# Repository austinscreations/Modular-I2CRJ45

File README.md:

# Modular-I2CRJ45
an oxrs compatible I2CRJ45 board in a modular format

2023-10-25 version 220 was created to fix p fet issue
also updated JLCPCB PCBa files for the modular I2CRJ45 and port PWR extention

this baord is 2 layers

port PWR is 2 layers

port PWR extention is a remote switch that allows you to turn ports on and off. the use of a 1.25mm jst cable could eb used instead, simply with pin 5 being GND connect the others to this and a port will be ON

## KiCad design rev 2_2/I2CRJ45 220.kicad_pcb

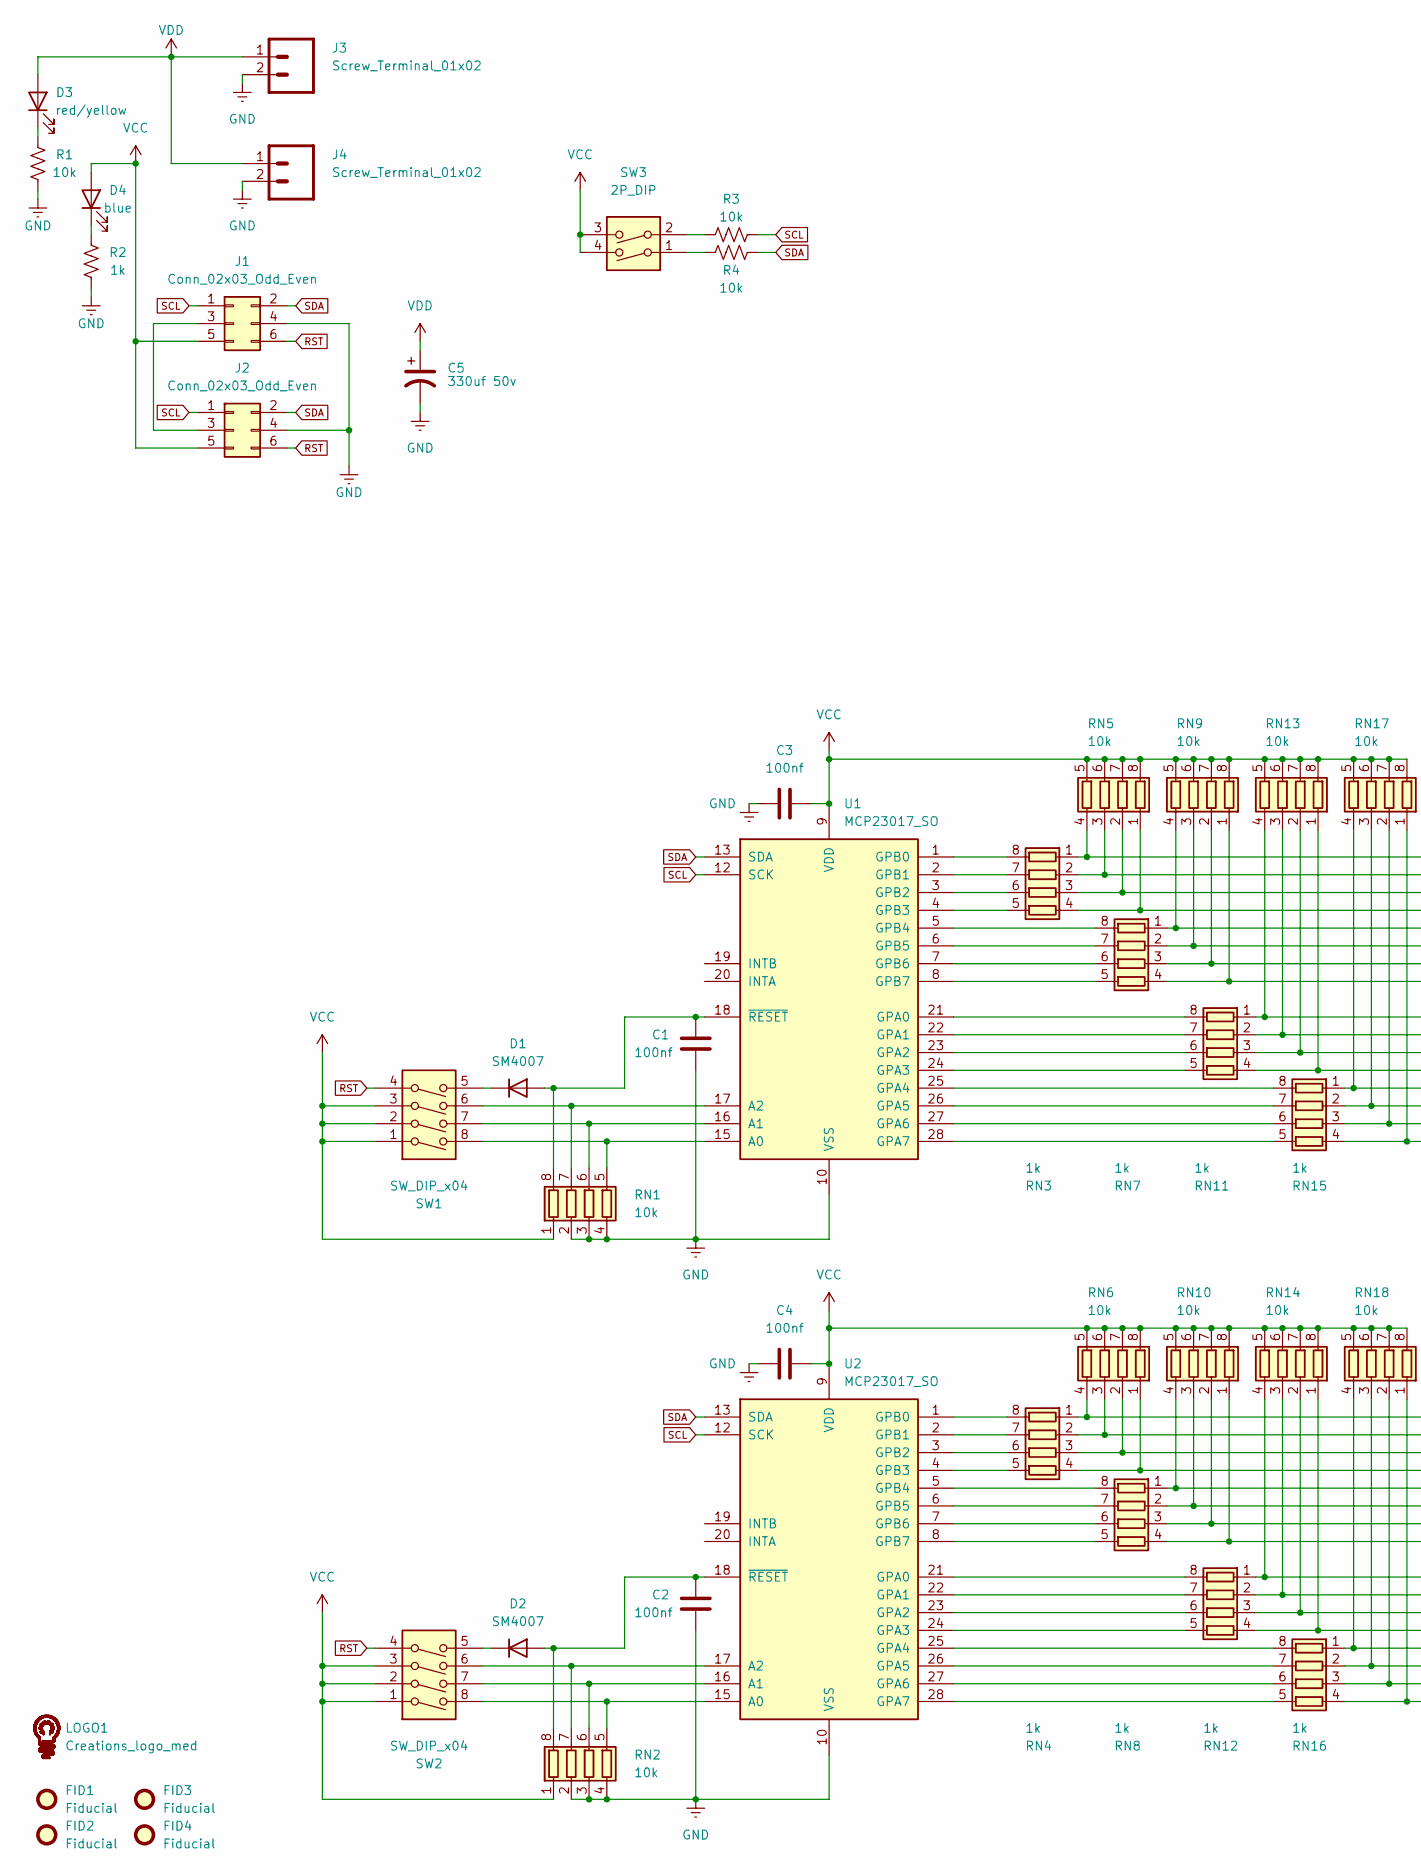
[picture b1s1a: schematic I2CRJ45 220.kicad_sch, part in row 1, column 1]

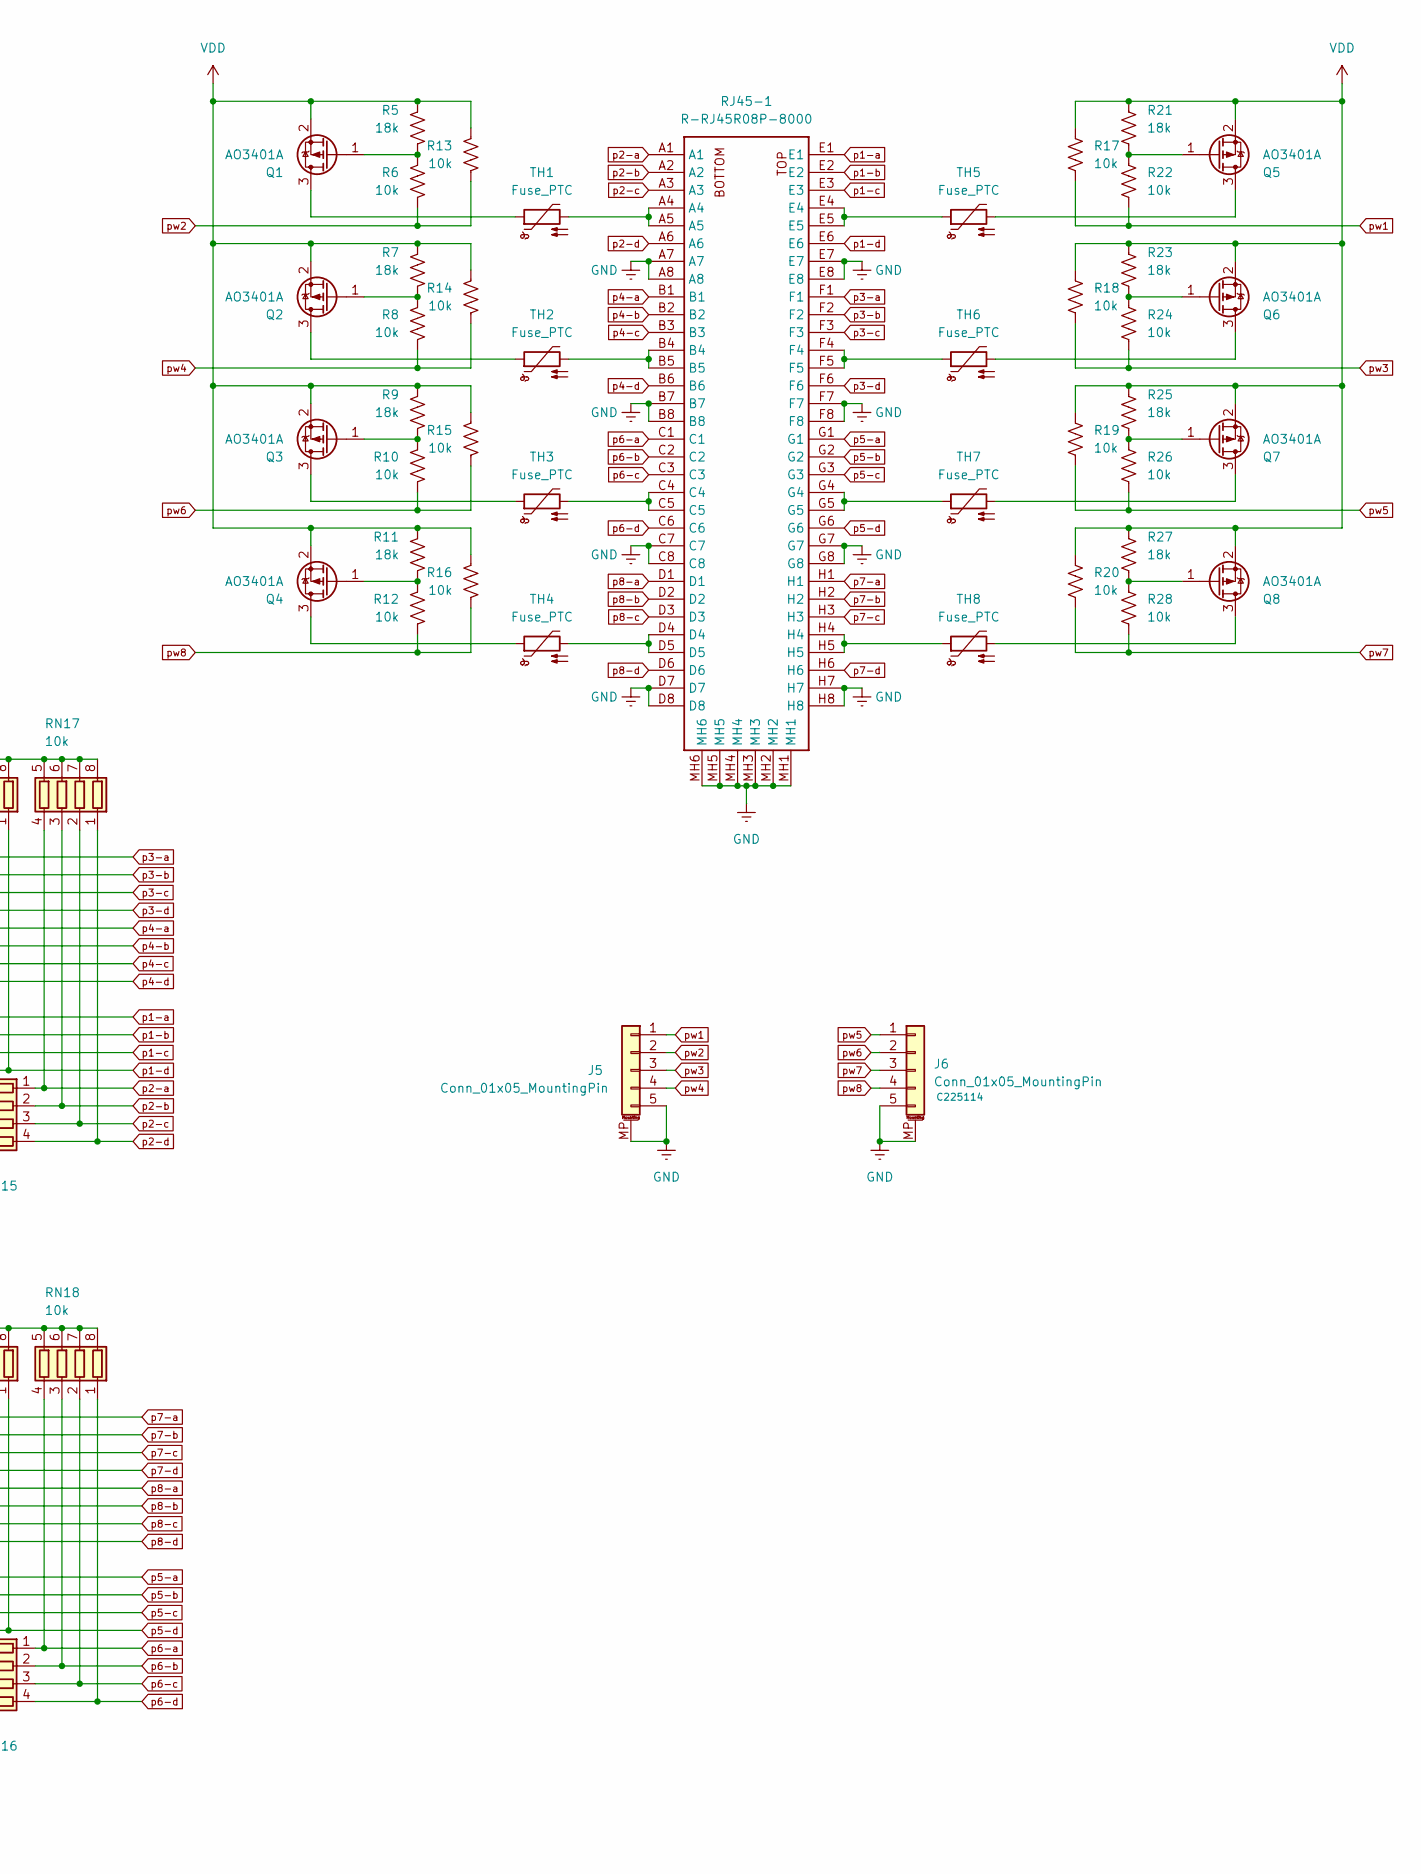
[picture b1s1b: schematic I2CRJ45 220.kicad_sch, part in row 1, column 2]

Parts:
C1, C2, C3, C4: 100nf; C_0603_1608Metric; LCSC C14663
C5: 330uf 50v; CP_Elec_10x10; LCSC C2895745
D1, D2: SM4007; D_SOD-123F; LCSC C64898
D3: red/yellow; LED_0603_1608Metric; LCSC C72038
D4: blue; LED_0603_1608Metric; LCSC C72041
FID1, FID2, FID3, FID4: Fiducial; Fiducial_1mm_Mask2mm
J1, J2: Conn_02x03_Odd_Even; IDC-Header_2x03_P2.54mm_Vertical; LCSC C132438
J3, J4: Screw_Terminal_01x02; 2pinblock; LCSC C3703
J5, J6: Conn_01x05_MountingPin; JST_GH_SM05B-GHS-TB_1x05-1MP_P1.25mm_Horizontal; LCSC C225114
LOGO1: Creations_logo_med; Creations logo med
Q1, Q2, Q3, Q4, Q5, Q6, Q7, Q8: AO3401A; SOT-23; LCSC C15127
R1, R3, R4, R6, R8, R10, R12, R13, R14, R15, R16, R17, R18, R19, R20, R22, R24, R26, R28: 10k; R_0603_1608Metric; LCSC C25804
R2: 1k; R_0603_1608Metric; LCSC C21190
R5, R7, R9, R11, R21, R23, R25, R27: 18k; R_0603_1608Metric; LCSC C25810
RJ45-1: R-RJ45R08P-8000; LCSC C386760
RN1, RN2, RN5, RN6, RN9, RN10, RN13, RN14, RN17, RN18: 10k; R_Array_Convex_4x0603; LCSC C29718
RN3, RN4, RN7, RN8, RN11, RN12, RN15, RN16: 1k; R_Array_Convex_4x0603; LCSC C20197
SW1, SW2: SW_DIP_x04; 4P_DIP; LCSC C2758183
SW3: 2P_DIP; LCSC C2758181
TH1, TH2, TH3, TH4, TH5, TH6, TH7, TH8: Fuse_PTC; R_0603_1608Metric; LCSC C883087
U1, U2: MCP23017_SO; SOIC-28W_7.5x17.9mm_P1.27mm; LCSC C47023

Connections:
GNDREF: C1.2, C2.2, C3.1, C4.1, C5.2, J1.4, J2.4, J3.2, J4.2, J5.5, J5.MP (MountPin), J6.5, J6.MP (MountPin), R1.2, R2.2, RJ45-1.A7, RJ45-1.A8, RJ45-1.B7, RJ45-1.B8, RJ45-1.C7, RJ45-1.C8, RJ45-1.D7, RJ45-1.D8, RJ45-1.E7, RJ45-1.E8, RJ45-1.F7, RJ45-1.F8, RJ45-1.G7, RJ45-1.G8, RJ45-1.H7, RJ45-1.H8, RJ45-1.MH1, RJ45-1.MH2, RJ45-1.MH3, RJ45-1.MH4, RJ45-1.MH5, RJ45-1.MH6, RN1.2 (R2.1), RN1.3 (R3.1), RN1.4 (R4.1), RN2.2 (R2.1), RN2.3 (R3.1), RN2.4 (R4.1), U1.10 (VSS), U2.10 (VSS)
unnamed: C1.1, D1.2 (A), RN1.8 (R1.2), U1.18 (~RESET)
unnamed: C2.1, D2.2 (A), RN2.8 (R1.2), U2.18 (~RESET)
unnamed: D1.1 (K), SW1.5
unnamed: D2.1 (K), SW2.5
unnamed: D3.1 (K), R1.1
unnamed: D4.1 (K), R2.1
unnamed: J1.3, J2.3
unnamed: Q1.1 (G), R5.2, R6.1
unnamed: Q2.1 (G), R7.2, R8.1
unnamed: Q3.1 (G), R9.2, R10.1
unnamed: Q4.1 (G), R11.2, R12.1
unnamed: Q5.1 (G), R21.2, R22.1
unnamed: Q6.1 (G), R23.2, R24.1
unnamed: Q7.1 (G), R25.2, R26.1
unnamed: Q8.1 (G), R27.2, R28.1
unnamed: R3.1, SW3.2
unnamed: R4.1, SW3.1
unnamed: RJ45-1.A4, RJ45-1.A5, TH1.2
unnamed: RJ45-1.B4, RJ45-1.B5, TH2.2
unnamed: RJ45-1.C4, RJ45-1.C5, TH3.2
unnamed: RJ45-1.D4, RJ45-1.D5, TH4.2
unnamed: RJ45-1.E4, RJ45-1.E5, TH5.1
unnamed: RJ45-1.F4, RJ45-1.F5, TH6.1
unnamed: RJ45-1.G4, RJ45-1.G5, TH7.1
unnamed: RJ45-1.H4, RJ45-1.H5, TH8.1
unnamed: RN1.5 (R4.2), SW1.8, U1.15 (A0)
unnamed: RN1.6 (R3.2), SW1.7, U1.16 (A1)
unnamed: RN1.7 (R2.2), SW1.6, U1.17 (A2)
unnamed: RN2.5 (R4.2), SW2.8, U2.15 (A0)
unnamed: RN2.6 (R3.2), SW2.7, U2.16 (A1)
unnamed: RN2.7 (R2.2), SW2.6, U2.17 (A2)
unnamed: RN3.5 (R4.2), U1.4 (GPB3)
unnamed: RN3.6 (R3.2), U1.3 (GPB2)
unnamed: RN3.7 (R2.2), U1.2 (GPB1)
unnamed: RN3.8 (R1.2), U1.1 (GPB0)
unnamed: RN4.5 (R4.2), U2.4 (GPB3)
unnamed: RN4.6 (R3.2), U2.3 (GPB2)
unnamed: RN4.7 (R2.2), U2.2 (GPB1)
unnamed: RN4.8 (R1.2), U2.1 (GPB0)
unnamed: RN7.5 (R4.2), U1.8 (GPB7)
unnamed: RN7.6 (R3.2), U1.7 (GPB6)
unnamed: RN7.7 (R2.2), U1.6 (GPB5)
unnamed: RN7.8 (R1.2), U1.5 (GPB4)
unnamed: RN8.5 (R4.2), U2.8 (GPB7)
unnamed: RN8.6 (R3.2), U2.7 (GPB6)
unnamed: RN8.7 (R2.2), U2.6 (GPB5)
unnamed: RN8.8 (R1.2), U2.5 (GPB4)
unnamed: RN11.5 (R4.2), U1.24 (GPA3)
unnamed: RN11.6 (R3.2), U1.23 (GPA2)
unnamed: RN11.7 (R2.2), U1.22 (GPA1)
unnamed: RN11.8 (R1.2), U1.21 (GPA0)
unnamed: RN12.5 (R4.2), U2.24 (GPA3)
unnamed: RN12.6 (R3.2), U2.23 (GPA2)
unnamed: RN12.7 (R2.2), U2.22 (GPA1)
unnamed: RN12.8 (R1.2), U2.21 (GPA0)
unnamed: RN15.5 (R4.2), U1.28 (GPA7)
unnamed: RN15.6 (R3.2), U1.27 (GPA6)
unnamed: RN15.7 (R2.2), U1.26 (GPA5)
unnamed: RN15.8 (R1.2), U1.25 (GPA4)
unnamed: RN16.5 (R4.2), U2.28 (GPA7)
unnamed: RN16.6 (R3.2), U2.27 (GPA6)
unnamed: RN16.7 (R2.2), U2.26 (GPA5)
unnamed: RN16.8 (R1.2), U2.25 (GPA4)
unnamed: Q1.3 (D), TH1.1
unnamed: Q2.3 (D), TH2.1
unnamed: Q3.3 (D), TH3.1
unnamed: Q4.3 (D), TH4.1
unnamed: Q5.3 (D), TH5.2
unnamed: Q6.3 (D), TH6.2
unnamed: Q7.3 (D), TH7.2
unnamed: Q8.3 (D), TH8.2
RST: J1.6, J2.6, SW1.4, SW2.4
SCL: J1.1, J2.1, R3.2, U1.12 (SCK), U2.12 (SCK)
SDA: J1.2, J2.2, R4.2, U1.13 (SDA), U2.13 (SDA)
VCC: C3.2, C4.2, D4.2 (A), J1.5, J2.5, RN1.1 (R1.1), RN2.1 (R1.1), RN5.5 (R4.2), RN5.6 (R3.2), RN5.7 (R2.2), RN5.8 (R1.2), RN6.5 (R4.2), RN6.6 (R3.2), RN6.7 (R2.2), RN6.8 (R1.2), RN9.5 (R4.2), RN9.6 (R3.2), RN9.7 (R2.2), RN9.8 (R1.2), RN10.5 (R4.2), RN10.6 (R3.2), RN10.7 (R2.2), RN10.8 (R1.2), RN13.5 (R4.2), RN13.6 (R3.2), RN13.7 (R2.2), RN13.8 (R1.2), RN14.5 (R4.2), RN14.6 (R3.2), RN14.7 (R2.2), RN14.8 (R1.2), RN17.5 (R4.2), RN17.6 (R3.2), RN17.7 (R2.2), RN17.8 (R1.2), RN18.5 (R4.2), RN18.6 (R3.2), RN18.7 (R2.2), RN18.8 (R1.2), SW1.1, SW1.2, SW1.3, SW2.1, SW2.2, SW2.3, SW3.3, SW3.4, U1.9 (VDD), U2.9 (VDD)
VDD: C5.1, D3.2 (A), J3.1, J4.1, Q1.2 (S), Q2.2 (S), Q3.2 (S), Q4.2 (S), Q5.2 (S), Q6.2 (S), Q7.2 (S), Q8.2 (S), R5.1, R7.1, R9.1, R11.1, R13.1, R14.1, R15.1, R16.1, R17.1, R18.1, R19.1, R20.1, R21.1, R23.1, R25.1, R27.1
p1-a: RJ45-1.E1, RN11.1 (R1.1), RN13.4 (R4.1)
p1-b: RJ45-1.E2, RN11.2 (R2.1), RN13.3 (R3.1)
p1-c: RJ45-1.E3, RN11.3 (R3.1), RN13.2 (R2.1)
p1-d: RJ45-1.E6, RN11.4 (R4.1), RN13.1 (R1.1)
p2-a: RJ45-1.A1, RN15.1 (R1.1), RN17.4 (R4.1)
p2-b: RJ45-1.A2, RN15.2 (R2.1), RN17.3 (R3.1)
p2-c: RJ45-1.A3, RN15.3 (R3.1), RN17.2 (R2.1)
p2-d: RJ45-1.A6, RN15.4 (R4.1), RN17.1 (R1.1)
p3-a: RJ45-1.F1, RN3.1 (R1.1), RN5.4 (R4.1)
p3-b: RJ45-1.F2, RN3.2 (R2.1), RN5.3 (R3.1)
p3-c: RJ45-1.F3, RN3.3 (R3.1), RN5.2 (R2.1)
p3-d: RJ45-1.F6, RN3.4 (R4.1), RN5.1 (R1.1)
p4-a: RJ45-1.B1, RN7.1 (R1.1), RN9.4 (R4.1)
p4-b: RJ45-1.B2, RN7.2 (R2.1), RN9.3 (R3.1)
p4-c: RJ45-1.B3, RN7.3 (R3.1), RN9.2 (R2.1)
p4-d: RJ45-1.B6, RN7.4 (R4.1), RN9.1 (R1.1)
p5-a: RJ45-1.G1, RN12.1 (R1.1), RN14.4 (R4.1)
p5-b: RJ45-1.G2, RN12.2 (R2.1), RN14.3 (R3.1)
p5-c: RJ45-1.G3, RN12.3 (R3.1), RN14.2 (R2.1)
p5-d: RJ45-1.G6, RN12.4 (R4.1), RN14.1 (R1.1)
p6-a: RJ45-1.C1, RN16.1 (R1.1), RN18.4 (R4.1)
p6-b: RJ45-1.C2, RN16.2 (R2.1), RN18.3 (R3.1)
p6-c: RJ45-1.C3, RN16.3 (R3.1), RN18.2 (R2.1)
p6-d: RJ45-1.C6, RN16.4 (R4.1), RN18.1 (R1.1)
p7-a: RJ45-1.H1, RN4.1 (R1.1), RN6.4 (R4.1)
p7-b: RJ45-1.H2, RN4.2 (R2.1), RN6.3 (R3.1)
p7-c: RJ45-1.H3, RN4.3 (R3.1), RN6.2 (R2.1)
p7-d: RJ45-1.H6, RN4.4 (R4.1), RN6.1 (R1.1)
p8-a: RJ45-1.D1, RN8.1 (R1.1), RN10.4 (R4.1)
p8-b: RJ45-1.D2, RN8.2 (R2.1), RN10.3 (R3.1)
p8-c: RJ45-1.D3, RN8.3 (R3.1), RN10.2 (R2.1)
p8-d: RJ45-1.D6, RN8.4 (R4.1), RN10.1 (R1.1)
pw1: J5.1, R17.2, R22.2
pw2: J5.2, R6.2, R13.2
pw3: J5.3, R18.2, R24.2
pw4: J5.4, R8.2, R14.2
pw5: J6.1, R19.2, R26.2
pw6: J6.2, R10.2, R15.2
pw7: J6.3, R20.2, R28.2
pw8: J6.4, R12.2, R16.2

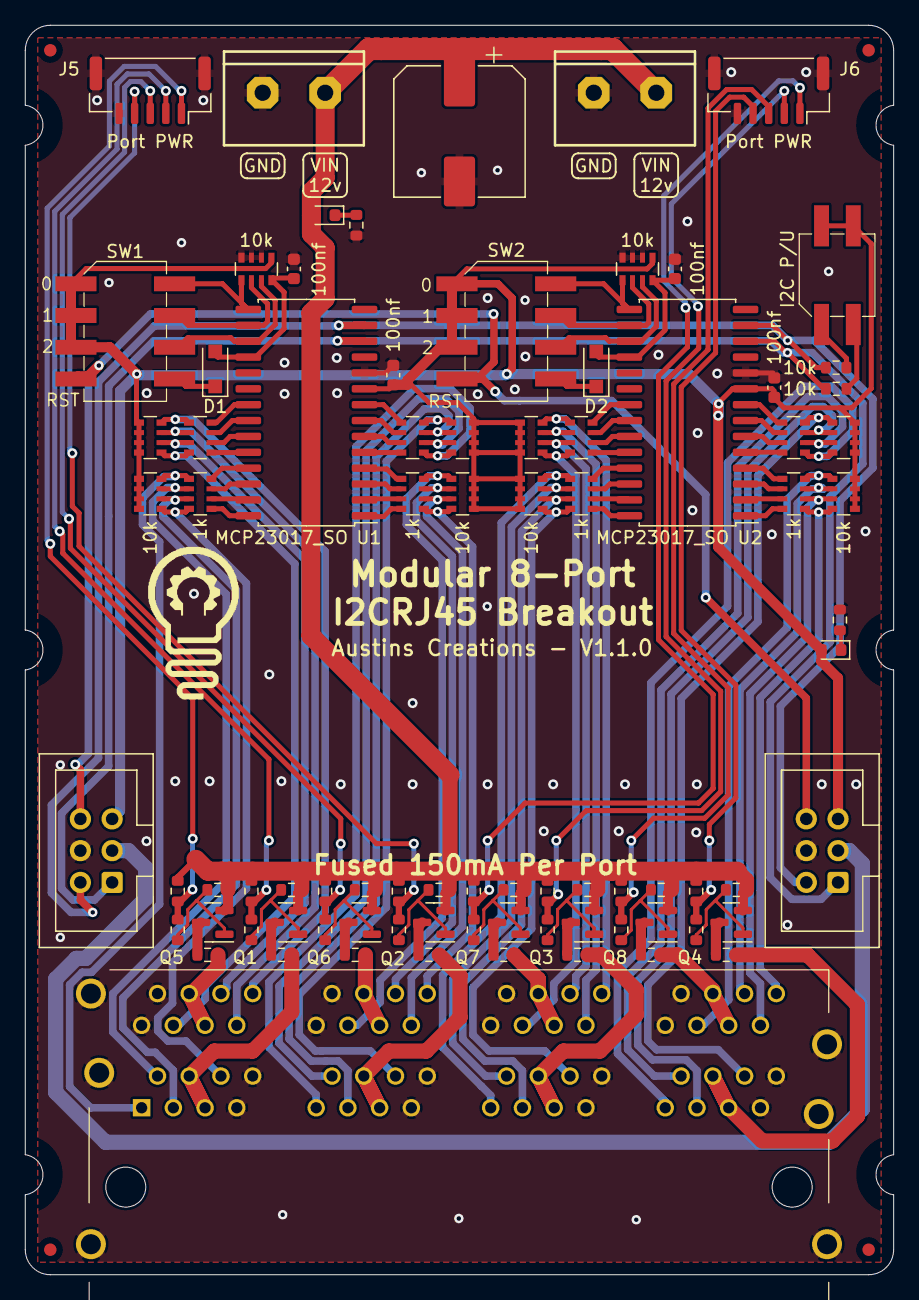
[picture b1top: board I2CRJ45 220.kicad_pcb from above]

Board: 2 copper layers, 69.5 x 100.0 mm, 88 parts (0 on the bottom side), 117 nets.

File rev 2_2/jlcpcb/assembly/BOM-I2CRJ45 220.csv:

Comment,Designator,Footprint,LCSC
Conn_02x03_Odd_Even,"J1,J2",IDC-Header_2x03_P2.54mm_Vertical,C132438
100nf,"C1,C2,C3,C4",C_0603_1608Metric,C14663
AO3401A,"Q1,Q2,Q3,Q4,Q5,Q6,Q7,Q8",SOT-23,C15127
1k,"RN11,RN12,RN15,RN16,RN3,RN4,RN7,RN8",R_Array_Convex_4x0603,C20197
1k,R2,R_0603_1608Metric,C21190
Conn_01x05_MountingPin,"J5,J6",JST_GH_SM05B-GHS-TB_1x05-1MP_P1.25mm_Horizontal,C225114
10k,"R1,R10,R12,R13,R14,R15,R16,R17,R18,R19,R20,R22,R24,R26,R28,R3,R4,R6,R8",R_0603_1608Metric,C25804 
18k,"R11,R21,R23,R25,R27,R5,R7,R9",R_0603_1608Metric,C25810
2P_DIP,SW3,2P_DIP,C2758181
SW_DIP_x04,"SW1,SW2",4P_DIP,C2758183
330uf 50v,C5,CP_Elec_10x10,C2895745
10k,"RN1,RN10,RN13,RN14,RN17,RN18,RN2,RN5,RN6,RN9",R_Array_Convex_4x0603,C29718
Screw_Terminal_01x02,"J3,J4",2pinblock,C3703
R-RJ45R08P-8000,RJ45-1,R-RJ45R08P-8000,C386760
MCP23017_SO,"U1,U2",SOIC-28W_7.5x17.9mm_P1.27mm,C47023
SM4007,"D1,D2",D_SOD-123F,C64898
red/yellow,D3,LED_0603_1608Metric,C72038
blue,D4,LED_0603_1608Metric,C72041
Fuse_PTC,"TH1,TH2,TH3,TH4,TH5,TH6,TH7,TH8",R_0603_1608Metric,C883087

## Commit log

2023-05-06 add 3d model
2023-05-07 add warning
2024-08-20 update d4 led to use JLCPCB part C2286
2024-08-20 update d4 led to use JLCPCB part C2286 (#1)

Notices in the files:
rev 2_2/I2CRJ45 220.kicad_pcb:
Copyright 2019-2021 SuperHouse Automation Pty Ltd
Open Hardware License: www.tapr.org/OHL
